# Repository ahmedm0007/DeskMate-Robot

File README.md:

# 🤖 DeskMate — Intelligent Study Assistant Robot

> A physical desktop robot that monitors student concentration in real time, detects distraction and fatigue, and provides personalized academic assistance through voice interaction and AI-powered document Q&A.

---

## 📌 Overview

DeskMate is an end-of-year engineering project built at **INSAT** (National Institute of Applied Science and Technology, Tunis). It addresses a concrete problem: study sessions are rarely as effective as they should be. Students get distracted, lose focus, and have no tool that actively intervenes.

DeskMate is a **physical companion robot** — present on your desk like a lamp — that observes, analyzes, and acts. Unlike passive apps, it adapts its behavior in real time to the student's actual state.

---

## ✨ Features

### 👁️ Behavioral Monitoring (Vision Pipeline)
- **Real-time face detection** and multi-user recognition (MediaPipe + ArcFace/DeepFace)
- **Fatigue detection** via Eye Aspect Ratio (EAR) and Mouth Aspect Ratio (MAR)
- **Distraction detection**: gaze direction (head pose estimation) + smartphone detection (YOLOv8)
- **Absence detection**: alerts when the student leaves the camera field
- Runs at **~30 FPS** on Raspberry Pi 4, well within the 500ms real-time constraint

### 🗣️ Voice Interaction (Vocal Pipeline)
- **Wake word detection** (local, via Vosk) → **Speech-to-Text** (Google Web Speech API)
- **LLM-powered intent classification** and conversational responses (Qwen2.5-7B-Instruct via Hugging Face API)
- **Text-to-Speech** output (edge_tts + pygame) with ~0.8s generation time
- End-to-end latency: **2–4 seconds** for a complete voice exchange

### 📚 Academic AI Assistant (RAG System)
- Upload your own **PDF course documents**
- Hybrid search: **semantic (ChromaDB)** + **keyword (BM25)** retrieval
- Answers generated by **Gemini 2.5 Flash**, grounded exclusively in your documents
- Evaluation results: **85% answer correctness**, 87.5% hit rate on test corpus

### 📅 Adaptive Study Planner
- Input your subjects, mastery level, exam dates, and available hours
- Generates a **personalized weekly revision schedule** using a priority scoring model
- Urgency factor recalculated daily as exams approach
- Subjects automatically removed after their exam date

### 📊 Session Management & Dashboard
- Supports **Pomodoro**, **Deep Work**, and **52/17** productivity techniques
- Voice-controlled session start/pause/stop
- OLED display shows current state (focused / distracted / break / session end)
- **React/Next.js web dashboard** (localhost): session history, productivity graphs, planning, PDF upload

### 🚗 Autonomous Mobility
- **Differential drive** (2× GA12-N20 motors) controlled by ESP32
- **ToF sensor (VL53L0X)** for desk-edge detection and collision avoidance
- Autonomous repositioning to keep the student in camera frame

---

## 🏗️ System Architecture

```
┌─────────────────────────────────────────────────────┐
│            LAYER 1 — Perception                     │
│   Pi Camera 8MP | INMP441 Mic (I2S) | ToF VL53L0X  │
└────────────────────┬────────────────────────────────┘
                     │
┌────────────────────▼────────────────────────────────┐
│          LAYER 2 — AI Processing                    │
│  OpenCV + YOLOv8 + MediaPipe (Vision)               │
│  Vosk + Google STT (Speech)                         │
│  LLM (Qwen2.5) + RAG (LangChain + ChromaDB)         │
└────────────────────┬────────────────────────────────┘
                     │
┌────────────────────▼────────────────────────────────┐
│       LAYER 3 — Decision & Orchestration            │
│       FastAPI — State machine | Scheduler | Rules   │
└────────────────────┬────────────────────────────────┘
                     │
┌────────────────────▼────────────────────────────────┐
│            LAYER 4 — Actuators                      │
│    GA12-N20 Motors | OLED SSD1306 | Speaker (TTS)   │
└────────────────────┬────────────────────────────────┘
                     │
┌────────────────────▼────────────────────────────────┐
│         LAYER 5 — User Interface (localhost)        │
│         React / Next.js + Tailwind CSS              │
│   History | Charts | Planning | PDF Upload | Profiles│
└─────────────────────────────────────────────────────┘
```

---

## 🔧 Hardware

| Component | Role |
|---|---|
| Raspberry Pi 4 (4GB) | Main brain — runs all AI/software modules |
| ESP32 | Spinal cord — real-time actuator control |
| Pi Camera Module V2 (8MP) | Vision pipeline input |
| INMP441 Microphone (I2S) | Voice capture |
| MAX98357A Amplifier + 8Ω Speaker | TTS audio output |
| OLED Display SSD1306 (0.96") | Real-time status display |
| ToF Sensor VL53L0X | Desk-edge detection |
| 2× GA12-N20 DC Motors + TB6612FNG | Differential drive |
| 2× 18650 Li-ion (3000 mAh) + XL4015 Buck | Power supply (~2.5–3.5h autonomy) |
| 3D-printed PLA chassis | 3-level structure, custom-designed |

---

## 💻 Tech Stack

**AI & Vision**
`OpenCV` `MediaPipe` `YOLOv8` `DeepFace (ArcFace)` `LangChain` `ChromaDB` `BM25` `Gemini 2.5 Flash` `Qwen2.5-7B`

**Speech**
`Vosk` `Google Web Speech API` `edge_tts` `pygame`

**Backend**
`FastAPI` `Python 3.10+` `SQLite` `PostgreSQL`

**Frontend**
`React 19` `Next.js` `TypeScript` `Tailwind CSS v4` `Recharts` `Vite`

**Embedded**
`Raspberry Pi OS` `ESP32 (Arduino)` `pigpio` `I2C` `I2S` `UART` `PWM`

**Design**
`SolidWorks` (3D chassis) `KiCad` (PCB schematic)

---

## 📈 Performance Results

| Module | Metric | Result |
|---|---|---|
| Vision pipeline | Processing speed | ~30 FPS on RPi 4 |
| Behavioral detection | Latency | < 500ms ✅ |
| Face recognition (ArcFace) | Accuracy | > 99% |
| Phone detection (YOLOv8) | mAP@50 | 52.1% (+ temporal smoothing) |
| RAG system | Answer correctness | 85.0% |
| RAG system | Hit rate | 87.5% |
| Voice pipeline | End-to-end latency | 2–4 seconds |
| TTS (edge_tts) | Generation time | ~0.8 seconds |

---

## 👥 Team

| Name | Role |
|---|---|
| **MAMI Ahmed** | Embedded systems, hardware design, mechanical conception |
| **ZGHIBI Ahmed** | AI pipeline, system integration |
| **EL KADHI Mohamed Amine** | Vision & RAG modules |
| **ZNAGUI Wael** | Backend & dashboard |

**Supervisor:** Mme JAAFAR Imen  
**Institution:** INSAT — 4th year, Industrial Computing and Automation  
**Defended:** June 1st, 2026

---

## 📄 License

This project was developed as an academic end-of-year project at INSAT, Tunis. All rights reserved by the authors.

## 🗂️ Mechanical Files (SolidWorks)

Full 3D assembly and parts (SolidWorks + STL) are too large for GitHub.  
👉 [Download 3D Files (Google Drive)] https://drive.google.com/drive/folders/134jamOGdysIHbzPeDwZQ4sSwSuv-kNpy?usp=sharing

Includes:
- Full robot assembly (RobotAssemblageV1.SLDASM)
- All individual parts (SLDPRT)
- STL files for 3D printing
- KiCad PCB schematic

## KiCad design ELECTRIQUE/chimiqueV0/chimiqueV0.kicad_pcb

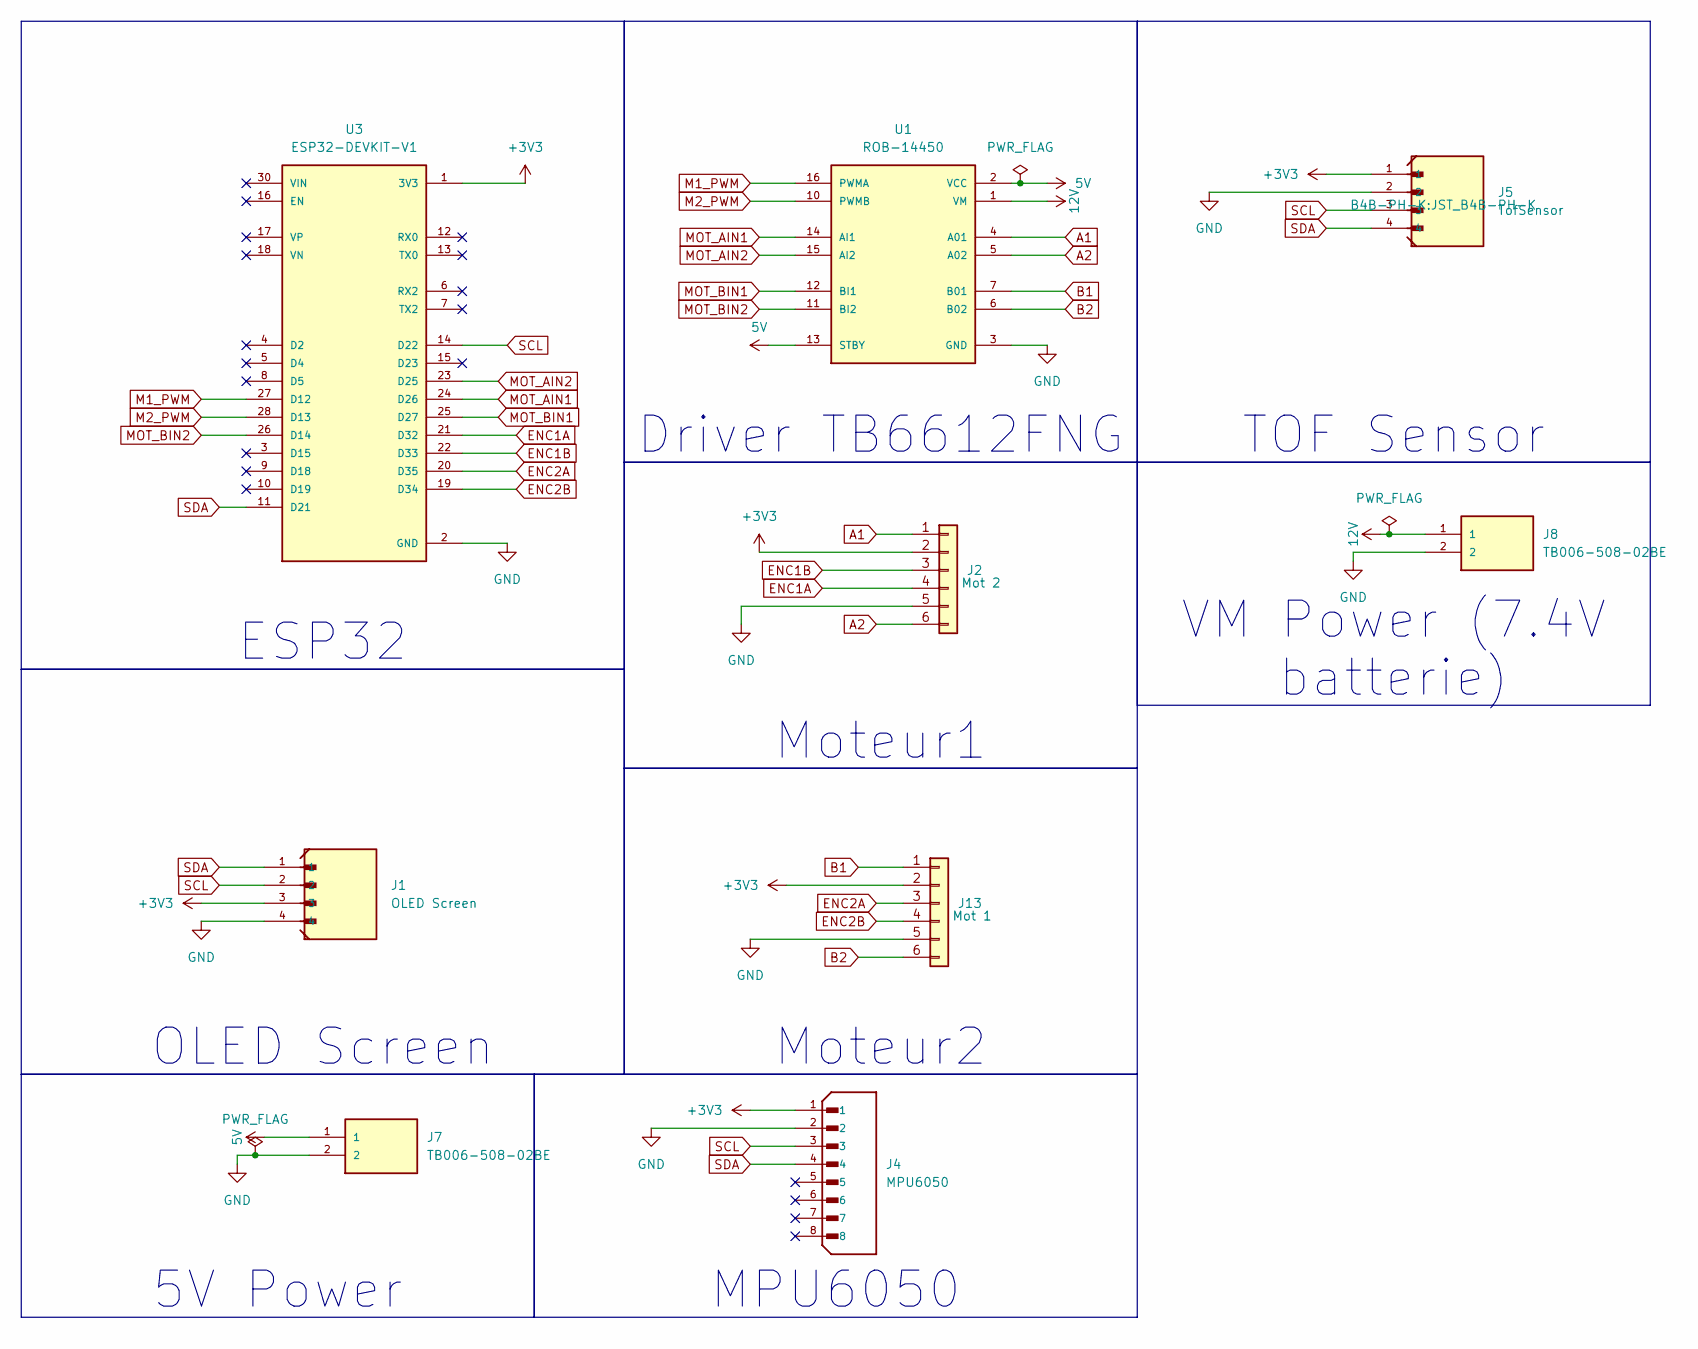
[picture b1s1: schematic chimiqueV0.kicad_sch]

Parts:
J1: OLED Screen; JST_B4B-PH-K
J2: Mot 2; JST_EH_B6B-EH-A_1x06_P2.50mm_Vertical
J4: MPU6050; JST_B8B-XH-A; PARTREV 7/4/21
J5: TofSensor; JST_B4B-PH-K
J7, J8: TB006-508-02BE; CUI_TB006-508-02BE
J13: Mot 1; JST_EH_B6B-EH-A_1x06_P2.50mm_Vertical
U1: ROB-14450; MODULE_ROB-14450; PARTREV 11-13-17
U3: ESP32-DEVKIT-V1; MODULE_ESP32_DEVKIT_V1; PARTREV N/A

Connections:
5V: J7.1, U1.2 (VCC), U1.13 (STBY)
12V: J8.1, U1.1 (VM)
+3V3: J1.3, J2.2, J4.1, J5.1, J13.2, U3.1 (3V3)
A1: J2.1, U1.4 (A01)
A2: J2.6, U1.5 (A02)
B1: J13.1, U1.7 (B01)
B2: J13.6, U1.6 (B02)
ENC1A: J2.4, U3.21 (D32)
ENC1B: J2.3, U3.22 (D33)
ENC2A: J13.3, U3.20 (D35)
ENC2B: J13.4, U3.19 (D34)
GND: J1.4, J2.5, J4.2, J5.2, J7.2, J8.2, J13.5, U1.3 (GND), U1.8 (GND), U1.9 (GND), U3.2 (GND), U3.29 (GND)
M1_PWM: U1.16 (PWMA), U3.27 (D12)
M2_PWM: U1.10 (PWMB), U3.28 (D13)
MOT_AIN1: U1.14 (AI1), U3.24 (D26)
MOT_AIN2: U1.15 (AI2), U3.23 (D25)
MOT_BIN1: U1.12 (BI1), U3.25 (D27)
MOT_BIN2: U1.11 (BI2), U3.26 (D14)
SCL: J1.2, J4.3, J5.3, U3.14 (D22)
SDA: J1.1, J4.4, J5.4, U3.11 (D21)

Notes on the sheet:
5V Power
Moteur2
ESP32
Driver TB6612FNG
Moteur1
MPU6050
OLED Screen
TOF Sensor
VM Power (7.4V batterie)

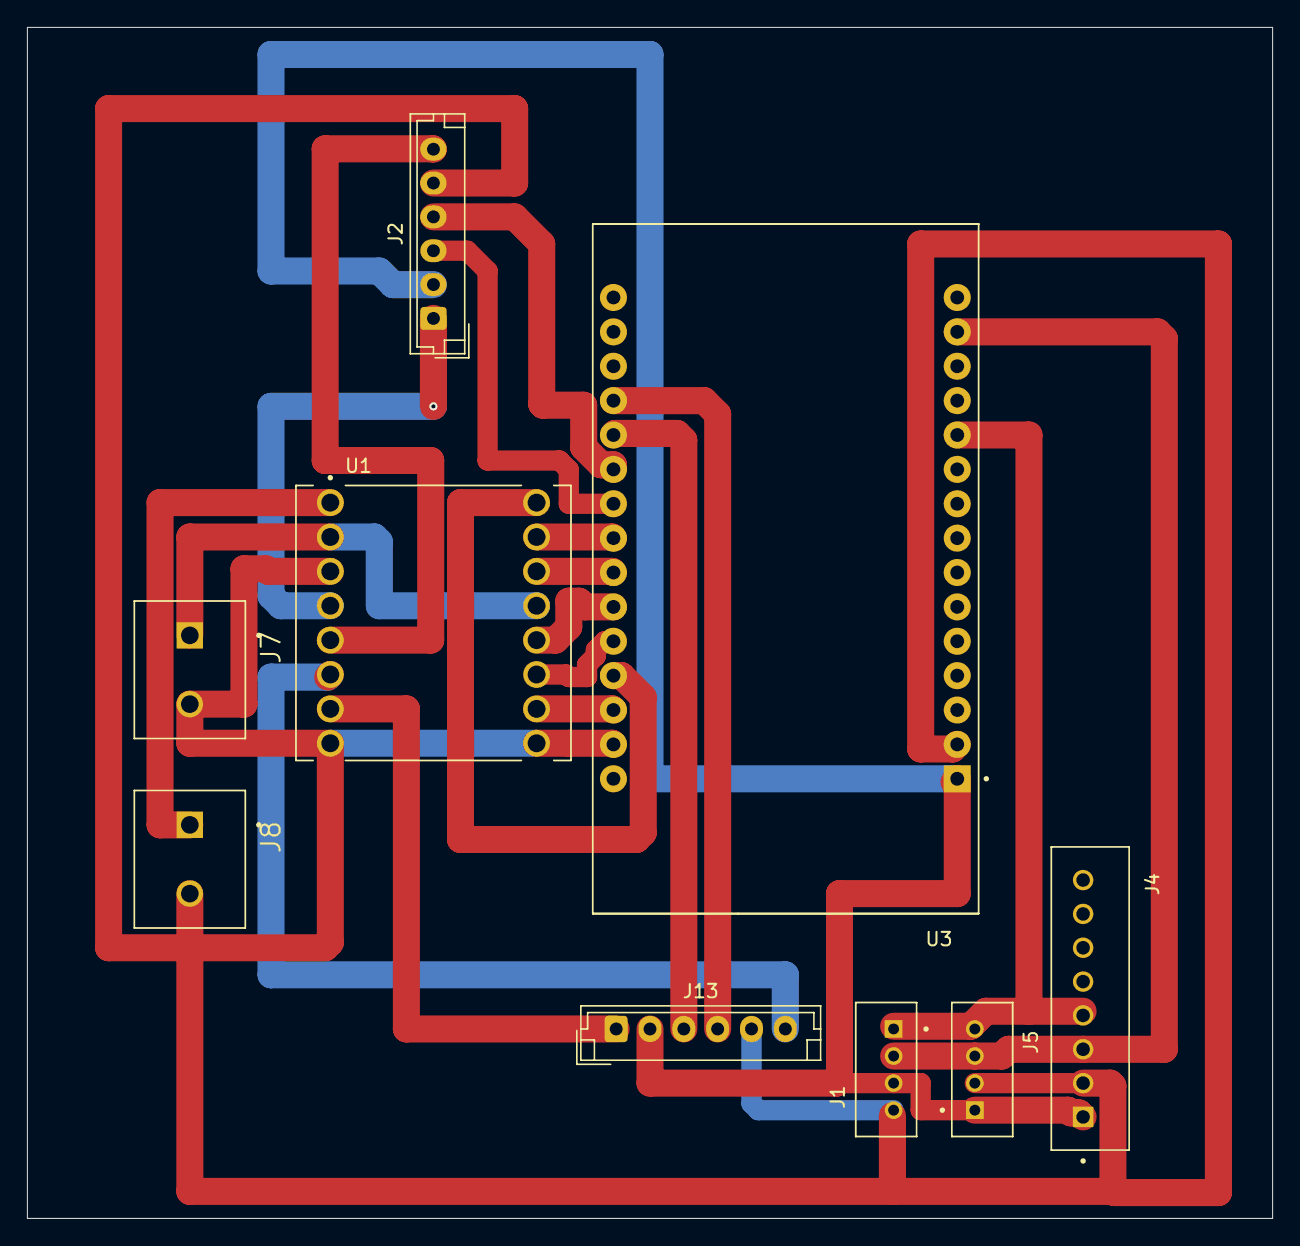
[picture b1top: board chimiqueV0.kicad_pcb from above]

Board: 2 copper layers, 92.0 x 88.0 mm, 9 parts (0 on the bottom side), 20 nets.

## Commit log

2026-06-06 Initial commit - DeskMate Robot
2026-06-06 Rename README
2026-06-06 Add mechanical files
2026-06-06 Add Google Drive link for mechanical files
